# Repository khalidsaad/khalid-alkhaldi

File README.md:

# khalid-alkhaldi
 DE0 GPIO to breadboard adapter

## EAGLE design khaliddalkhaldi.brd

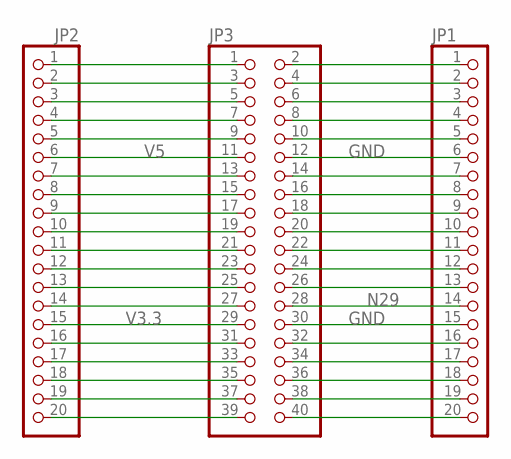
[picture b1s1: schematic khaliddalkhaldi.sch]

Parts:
JP1, JP2: PINHD-1X20; 1X20
JP3: PINHD-2X20; 2X20

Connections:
GND: JP1.6, JP1.15, JP3.12, JP3.30
N29: JP1.14, JP3.28
unnamed: JP2.1, JP3.1
unnamed: JP2.2, JP3.3
unnamed: JP2.3, JP3.5
unnamed: JP2.4, JP3.7
unnamed: JP2.5, JP3.9
unnamed: JP2.7, JP3.13
unnamed: JP2.8, JP3.15
unnamed: JP2.9, JP3.17
unnamed: JP2.10, JP3.19
unnamed: JP2.11, JP3.21
unnamed: JP2.12, JP3.23
unnamed: JP2.13, JP3.25
unnamed: JP2.14, JP3.27
unnamed: JP2.16, JP3.31
unnamed: JP2.17, JP3.33
unnamed: JP2.18, JP3.35
unnamed: JP2.19, JP3.37
unnamed: JP2.20, JP3.39
unnamed: JP1.20, JP3.40
unnamed: JP1.19, JP3.38
unnamed: JP1.18, JP3.36
unnamed: JP1.17, JP3.34
unnamed: JP1.16, JP3.32
unnamed: JP1.13, JP3.26
unnamed: JP1.12, JP3.24
unnamed: JP1.11, JP3.22
unnamed: JP1.10, JP3.20
unnamed: JP1.9, JP3.18
unnamed: JP1.8, JP3.16
unnamed: JP1.7, JP3.14
unnamed: JP1.5, JP3.10
unnamed: JP1.4, JP3.8
unnamed: JP1.3, JP3.6
unnamed: JP1.2, JP3.4
unnamed: JP1.1, JP3.2
V3.3: JP2.15, JP3.29
V5: JP2.6, JP3.11

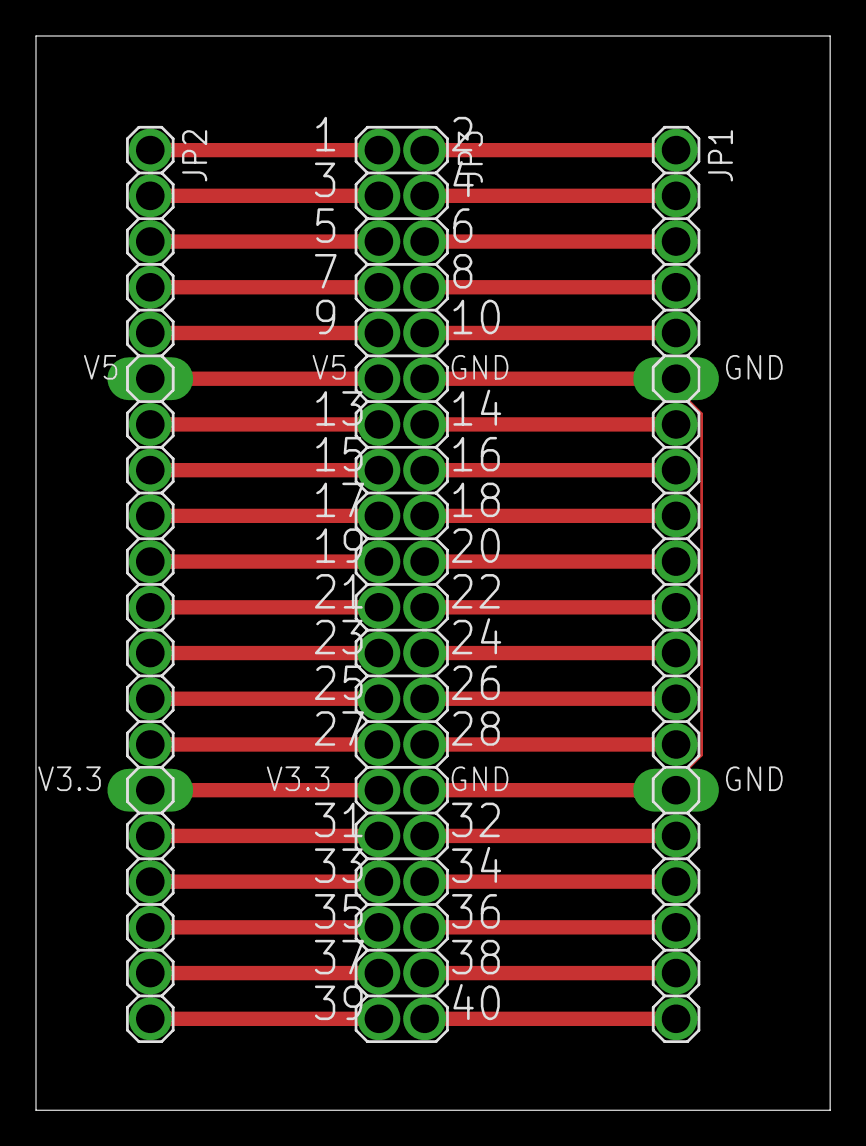
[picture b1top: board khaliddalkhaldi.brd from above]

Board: 2 copper layers, 44.1 x 59.7 mm, 3 parts (0 on the bottom side), 39 nets.
